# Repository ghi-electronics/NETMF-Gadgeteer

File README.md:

# NETMF-Gadgeteer

This is the repository for our .NET Gadgeteer drivers. While we are keeping it up, it is no longer being actively maintained.

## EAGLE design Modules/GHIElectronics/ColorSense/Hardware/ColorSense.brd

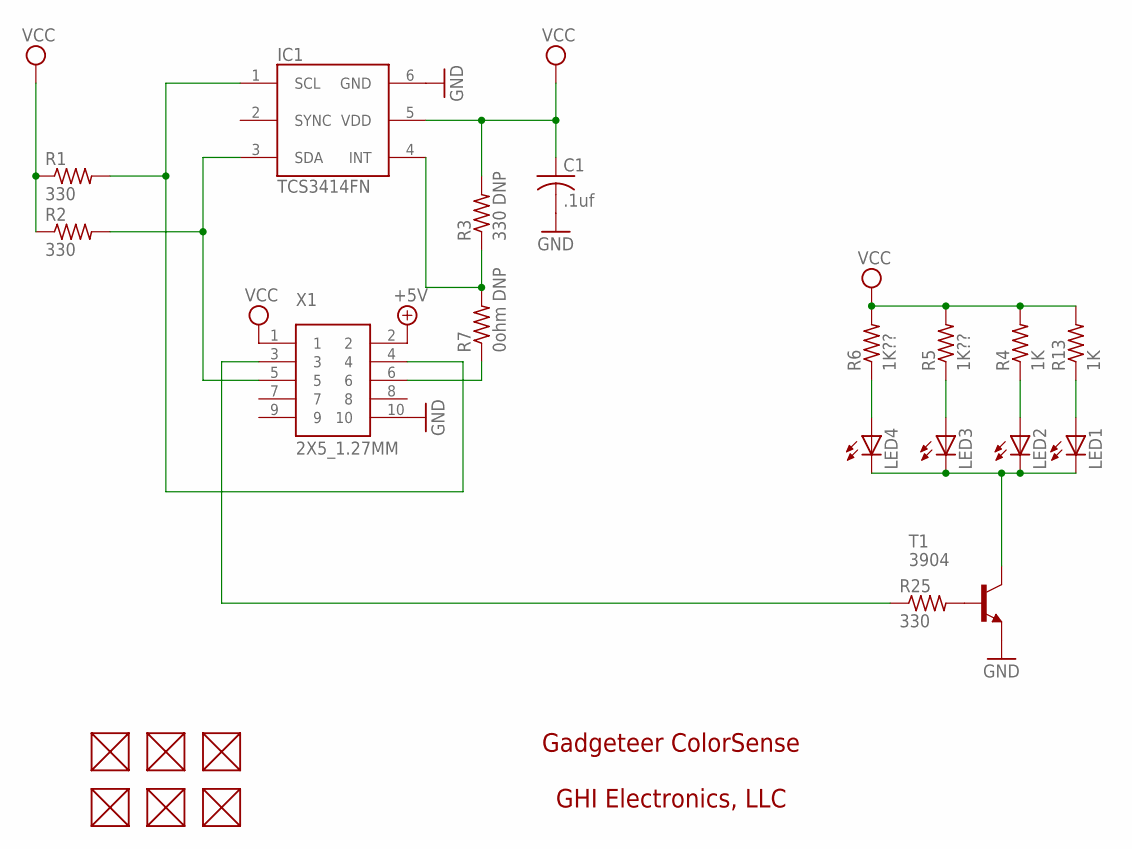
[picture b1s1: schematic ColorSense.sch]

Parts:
C1: .1uf; C0603K
FUD1, FUD2, FUD3, FUD4, FUD5, FUD6: FIDUCIAL; FIDUCIAL_40MIL
IC1: TCS3414FN; DFN-6
LED1, LED2, LED3, LED4: LEDCHIPLED_0805; CHIPLED_0805
R1, R2, R25: 330; R0603
R3: 330 DNP; R0603
R4, R13: 1K; R0603
R5, R6: 1K??; R0603
R7: 0ohm DNP; R0603
T1: 3904; SOT23-BEC
X1: 2X5_1.27MM

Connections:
+5V: X1.2
BACKLIGHT: R25.1, X1.3
GND: C1.2, IC1.6 (GND), T1.E, X1.10
LED-: LED1.C, LED2.C, LED3.C, LED4.C, T1.C
unnamed: IC1.4 (INT), R3.1, R7.2
unnamed: IC1.3 (SDA), R2.2, X1.5
unnamed: IC1.1 (SCL), R1.2, X1.4
unnamed: R7.1, X1.6
unnamed: LED2.A, R4.1
unnamed: LED3.A, R5.1
unnamed: LED4.A, R6.1
unnamed: LED1.A, R13.1
unnamed: R25.2, T1.B
VCC: C1.1, IC1.5 (VDD), R1.1, R2.1, R3.2, R4.2, R5.2, R6.2, R13.2, X1.1

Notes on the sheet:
Gadgeteer ColorSense
GHI Electronics, LLC

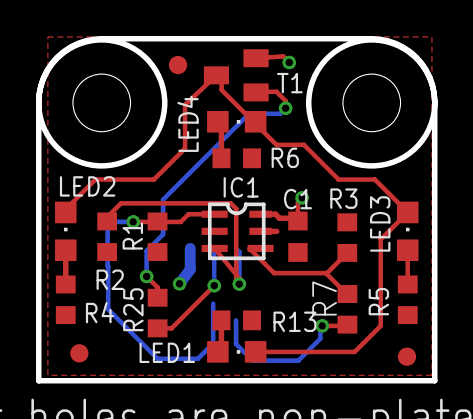
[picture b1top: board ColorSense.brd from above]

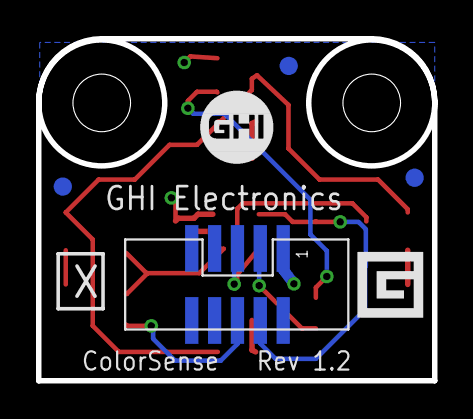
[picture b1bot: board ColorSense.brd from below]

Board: 2 copper layers, 22.0 x 19.0 mm, 23 parts (4 on the bottom side), 13 nets.

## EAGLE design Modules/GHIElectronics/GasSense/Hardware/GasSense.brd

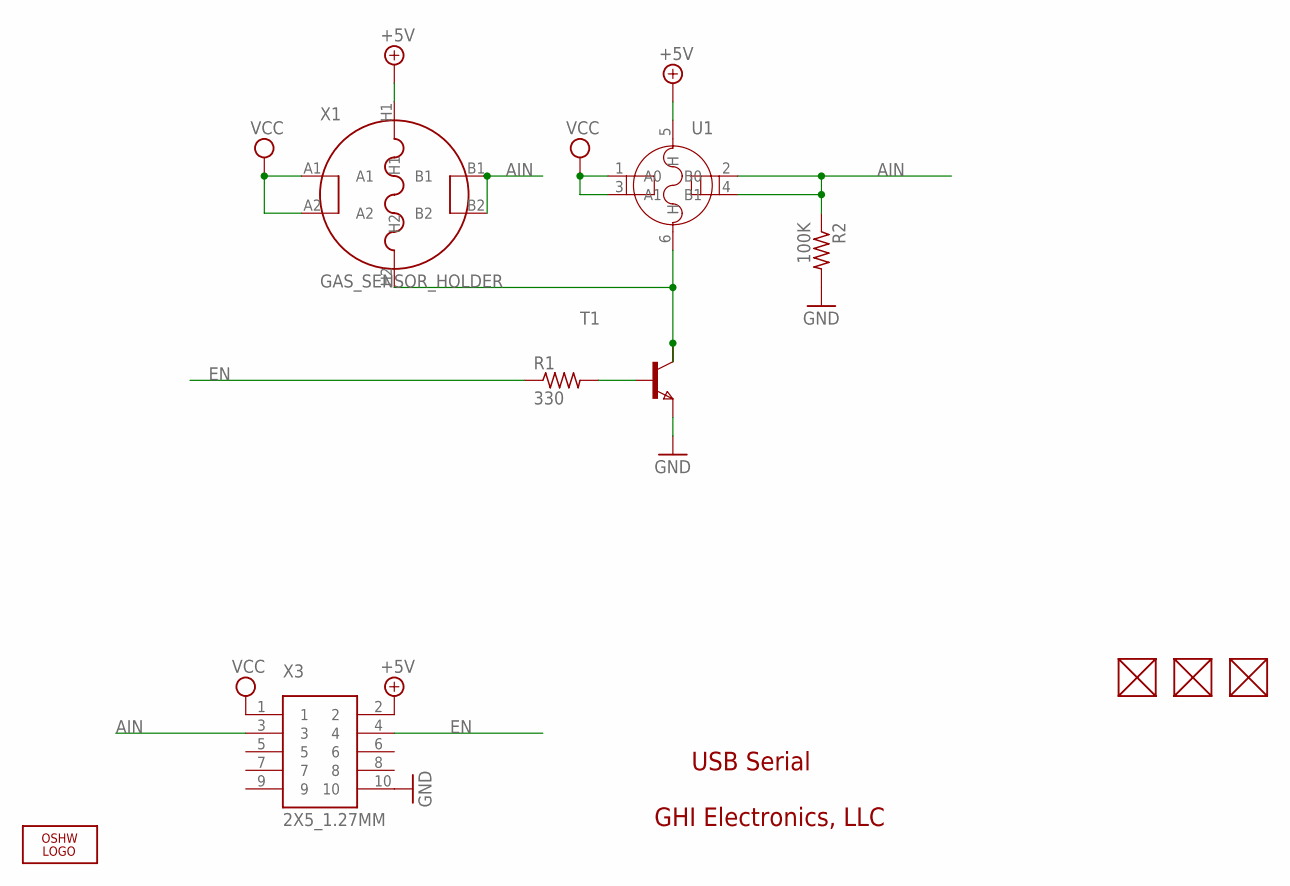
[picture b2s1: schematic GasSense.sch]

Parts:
FUD1, FUD2, FUD3: FIDUCIAL; FIDUCIAL_40MIL
LOGO1: LOGO-OSHW-FILLX0200-NT; OSHW_FILLX200_NOTEXT
R1: 330; R0603
R2: 100K; R0603
T1: NPNSOT223; SOT223
U1: SENSOR-MQ-5; 6P-LEADED-ROUND-D19
X1: GAS_SENSOR_HOLDER
X3: 2X5_1.27MM

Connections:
+5V: U1.5 (H), X1.H1, X3.2
AIN: R2.1, U1.2 (B0), U1.4 (B1), X1.B1, X1.B2, X3.3
EN: R1.1, X3.4
GND: R2.2, T1.3 (E), X3.10
unnamed: R1.2, T1.1 (B)
unnamed: T1.2 (C1), T1.4 (C2), U1.6 (H), X1.H2
VCC: U1.1 (A0), U1.3 (A1), X1.A1, X1.A2, X3.1

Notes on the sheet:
USB Serial
GHI Electronics, LLC

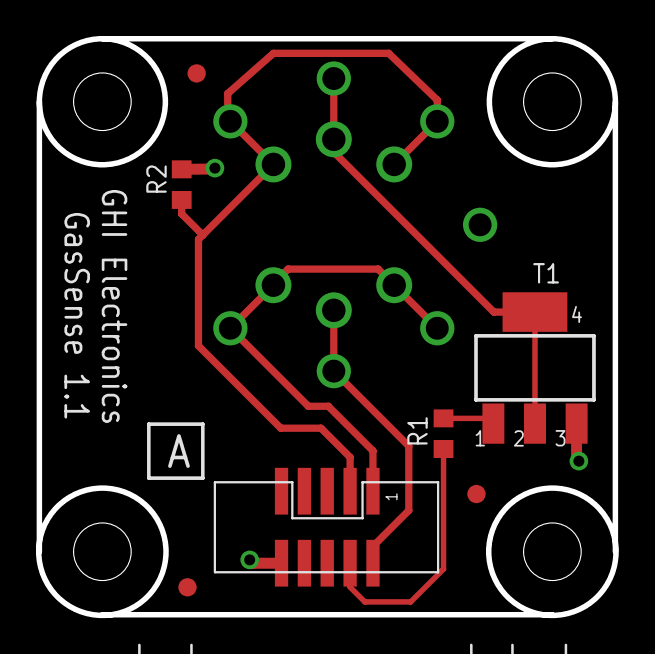
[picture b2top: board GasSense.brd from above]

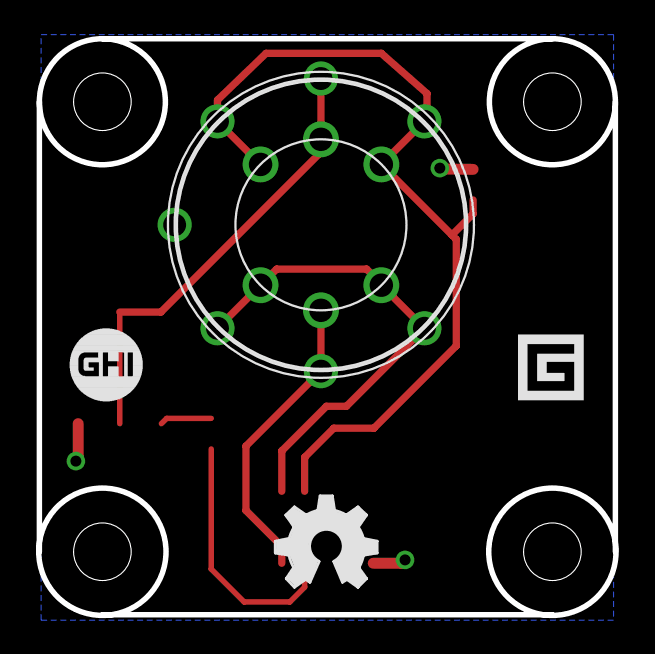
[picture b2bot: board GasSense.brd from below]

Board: 2 copper layers, 32.1 x 32.0 mm, 10 parts (3 on the bottom side), 7 nets.

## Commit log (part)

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2013-07-11 NET-24 #resolve Added ReflectorR3 tester and driver.
2013-07-11 Renamed the TouchC8 buttons.
2013-07-11 NET-27 #resolve Added RS485 tester and driver.
2013-07-15 Removed flow control from the port initialization in RS485.
2013-07-15 NET-23 #comment Started progress on the DAQ driver, still no response from the device.
2013-07-15 Fixed TouchC8 and TouchL12 power ratings.
2013-07-19 Updated RS485 driver.
2013-07-19 Re-added GetJoystickPosition() but marked it as obsolete.
2013-07-22 Updated some project files.
2013-07-22 #NET-51 Added some module images.
2013-07-22 Fixed an issue with WiFi_RN171/GadgeteerHardware.xml where it incorrectly only accepted a K type socket.
2013-07-25 Polished HubAP5 a bit.
2013-07-26 Fixed error messages for AnalogOutput.
2013-07-26 NET-46 #resolve Updated the SDK to Gadgeteer core version 800.
2013-07-31 Fixed a casting issue.
2013-08-07 Fixed the Tunes playback thread.
2013-08-14 Fixed a few socket type bugs in CerbuinoNet and Spider II.
2013-08-15 Updated DisplayN18 solution.
2013-08-15 Fixed TouchL12 guids.
2013-08-15 Fixed Spider II directory structure.
2013-08-15 Added FEZtive to the SDK.
2013-08-15 Fixed FEZtive_42.cs SetAll(Color[]) function
2013-08-19 Updated files for next beta attempt.
2013-08-23 Various bug fixes and tweaks for the SDK.
2013-08-27 Updated Spider II pins and image and updated HubAP5 so that glitchFilter = on no longer throws an exception.
2013-09-04 Increased the CP7 pixel clock divider to 5 from 3 as it was giving trouble with the G120.
2013-09-04 Fixed a bug with socket numbers and premium libraries for the Raptor.
2013-09-11 NET-102 #resolve Worked around the Gadgeteer SPI bug in the music module.
2013-09-11 NET-90 #resolve Added channel band and spacing control.
2013-09-18 NET-38 Added ButtonS7 image, added EnsureTypeIsSupported, and fix socket position.
2013-09-18 Fixed SpiderII AOut precision.
2013-09-20 Removed the ReadMe files.
2013-09-25 NET-23 Added DAQ8B module. Still needs image.
2013-10-01 MET-120 #resolve Fixed the DAQ channels.
2013-10-03 Fixed Cobra II and RN171 shared pins.
2013-10-11 Fixed Display N7 corruption on G120.
2013-10-23 Updated release notes and remopved pull down resistors from the DistanceUS3.
2013-11-18 Fixed Raptor bitmap callback.
2013-12-09 NET-40 #resolve Added a controllable frequency and improved the non-blocking function for the MotorController.
2013-12-11 Removed the pull down resistors from ButtonS7 and improved HubAP5 a bit.
2014-01-03 Fixed a null reference exception in Tunes.Stop
2014-01-07 Removed an un-needed pin reservation.
2014-01-16 NET-127 Added 4.3 projects for each module and mainboard. Still need to be updated to the Gadgeteer 4.3 API.
2014-01-17 Updated drivers to the 4.3 Gadgeteer API.
2014-01-20 NET-127 Updated the copyright year and assembly versioning.
2014-01-20 NET-127 Updated the MSI and MSM files.
2014-01-20 NET-127 Updated GadgeteerHardware.
2014-01-21 NET-127 Updated some installer projects.
2014-01-28 Updated release notes.
2014-01-30 Added SPlus assembly info.
2014-02-06 Fixed some bugs in RN171
2014-02-13 Updated some mainboard Gadgeteer hardware files.
2014-02-13 Updated GHI libraries to use underscores.
2014-02-18 Removed unneeded icons.
2014-02-19 Updated some Gadgeteer hardware files for 4.2.
2014-02-19 Moved the ELM and WiFly shared code into each NETMF version project because they are dependent on Gadgeteer.
2014-02-19 Added some old modules back.
2014-02-19 Lowercased instance name of modules.
2014-02-19 Added some missing things to the msm files.
2014-02-20 Updated some references.
2014-02-20 Few tweaks to GadgeteerHardwares.
2014-02-27 Updated some project references.
2014-02-28 Updated assembly references to use the new assemblies with periods.
2014-02-28 Corrected some assembly names.
2014-03-13 Removed Ref.s to TinyCLR
2014-03-26 Removed some discontinued modules.
2014-03-26 Removed LEDMatrix.
2014-03-26 NET-184 #resolve Fixed DaisyLink sockets in GadgeteerHardware.xml
2014-03-27 Updated the modules to use the new libraries.
2014-04-08 Updated mainboards to use the module shared files when possible and updated to the latest GHI libraries.
2014-04-14 Improved the Hydra, Raptor, Spider, and Spider II mainboards.
2014-04-15 Improved the Cobra and Cerberus mainboards.
2014-04-15 Improved the networking modules.
2014-04-15 Improved the displays.
2014-04-15 Improved the LED modules.
2014-04-15 Improved the relays.
2014-04-15 Improved USBHost.
2014-04-16 Improved the camera.
2014-04-16 Improved the flash module.
2014-04-17 Improved the RS485 and RS232.
2014-04-17 Improved the USBClient DP and SP.
2014-04-17 Improved some more modules.
2014-04-18 Improved PulseInOut and RadioFM1.
2014-04-18 Improved VideoOut and OBDII.
2014-04-18 Removed EVE800.
2014-04-18 Added the NullModem driver.
2014-04-18 Added an indirected socket to the extender.
2014-04-21 Improved the music module.
2014-04-21 Improved the GPS and Gyro.
2014-04-21 Updated the hardware versions in the Stepper and WiFi.
2014-04-22 Improved WiFiRN171 some.
2014-04-23 Finished improving the WiFi RN171.
2014-04-23 Fixed some event bugs in the CP7.
2014-04-28 A few bug fixes.
2014-04-29 Fixed some project references and updated versions.
2014-05-01 Fixed socket order in the G400HDR.
2014-05-13 Fixed a few driver bugs.
2014-05-13 Removes the font and resource files from the testers.
2014-05-28 Added the RelayX1 tester.
2014-05-28 Re-added the relay tester.
2014-05-28 Updated the mainboard testers.
2014-05-28 Added startup info to all of the module testers.
2014-05-28 updated some testers.
2014-05-30 Changed the font used in testers.
2014-06-02 Added ButtonS7 tester.
2014-06-11 Added Cerberus 4.3 mainboards.
2014-06-12 Fixed some tunes bugs and added a tester for it.
2014-06-17 Moved a lot of drivers to a legacy SDK.
2014-06-17 Moved Cobra II to legacy.
2014-06-17 Refactored some Seeed modules.
2014-06-18 Added more legacy modules to the Gadgeteer Legacy SDK.
2014-06-18 Fixed some paths in the legacy drivers.
2014-06-18 * Improve SerCam driver
2014-06-19 Improved SerCam Driver
2014-06-19 Tweaked SerCam exception.
2014-06-19 Added some testers.
2014-06-20 Fixed Cobra II Eco and added some testers.
2014-06-24 Added LightSense tester.
2014-06-25 Fixed setting the display orientation.
2014-06-25 Updated testers to 4.3.2.0 and added USBHost tester.
2014-07-07 Added the Button tester.
2014-07-16 Few bug fixes.
2014-07-17 Tweaked the AccelG248 and added a tester for it.
2014-07-17 Tweaked a tester.
2014-07-18 Improved the RFID reader.
2014-07-22 Updated to latest drivers and removed TempHumidity.
2014-07-22 Added TempHumidity to the legacy SDK.
2014-07-24 Defaulted to 9800 baud for serial and changed TempHumidSI70 to XY socket.
2014-07-24 Added SDCard features to Cobra II.
2014-07-24 Mounting and unmounting SD cards return bools.
2014-07-24 Improved storage device handling in the mainboards.
2014-07-24 Start the USB controller by default.
2014-07-25 Improved the USBHost and SDCard modules.
2014-07-25 Cleaned up SDCard support for the Cerbuinos and CobraII.
2014-07-25 Added USBHost to the Cerbuinos and Cobra II.
2014-07-29 Fixed SD card detection pin, updated some legacy mainboards, updated versions.
2014-07-30 Removed the mass storage mount functions from the boards with USB since its redundant and changed the SDCard detect on the Cobra to be an input port since its pin doesn't support interrupts.
2014-07-31 Added HubAP5 tester and updated DisplayTE35 tester.
2014-07-31 Updated some instruction text.
2014-08-01 Removed XBeeLib.
2014-08-07 Updated TempHumidSI70 tester.
2014-08-07 Updated TempHumidSI70 image.
2014-08-14 Fixed a bug in camera streaming.
2014-08-19 Fixed a socket bug.
2014-08-20 Added pin definitions for the header rows of the Cerbuinos.
2014-08-20 No longer open the network interface in the module constructor. Gives the user a chance to set the mac address.
2014-08-21 Properly set the control pin in Cerberus native spi display handler.
2014-08-21 Added a missing pin to a tester.
2014-08-21 Changed the legacy folders to discontinued and removed the legacy mainboards.
2014-08-28 Added the Hydra tester.
2014-09-03 Added USBHost to the Cerb Family boards and updated the versions.
2014-09-11 Fixed the extender socket and removed the text from the FEZ Spider image.
2014-09-16 Added a WiFiRS21 tester.
2014-09-18 Added USBSerialSP tester.
2014-10-01 Reduced a lot of the module and mainboard image sizes.
2014-10-13 Fixed a version number.
2014-10-13 Added a delay to SD card mounting.
2014-10-15 Cleaned up the cellular radio driver some.
2014-10-21 Fixed a reference version.
2014-10-22 Updated version.
2014-10-23 Fixed Extender analog in and out.
2014-11-20 Switched to context 1 in cellular radio.
2014-11-21 Fixed the COM port on socket 1 of the Cerbuino Net.
2014-11-21 Reworked response parsing on the cellular radio module.
2014-11-25 Added the discontinued modules to the main SDK but marked them as obsolete.
2014-11-25 Marked the Cobra IIs obsolete.
2014-11-25 Added 4.3 to some obsolete drivers.
2014-11-25 Cleaned up a few modules.
2014-11-26 Fixed two music module bugs.
2014-12-02 Fixed 4.3 cerb family analog output.
2014-12-03 Fixed some CurrentACS issues.
2014-12-04 Fixed a typo in CurrentACS.
2014-12-09 Changed the duty cycle after the tunes is done playing to stop a low hum from being improperly played.
2014-12-17 Improved SMS handling in the cellular radio.
2015-01-05 Fixed infinite playing and a variable name in Tunes.
2015-01-06 Fixed some reference versions.
2015-01-09 Fixed HD44780 image orientation.
2015-01-12 Fixed help urls.
2015-01-13 Fixed EBlockExpansion hardware definition file.
2015-02-04 Fixed the USB Client EDP hardware file.
2015-02-24 Fixed handling of counts around 0 in the RotaryEncoder.
2015-03-09 Allowed use of all clock sources in the Hub AP5 for better PWM generation.
2015-03-17 Removed a version attribute.
2015-03-18 Added a solution file.
2015-03-30 Formatted the 4.3 drivers.
2015-03-31 Fixed the rest tone in Tunes.
2015-04-03 Fixed Display T35 display name.
2015-04-08 Fixed Hydra supported socket types.
2015-04-09 Added an overload to allow customizing PPP initialization.
2015-04-09 Added SendATCommand with expected response.
2015-04-09 Fixed the power up state check.
2015-04-09 Fixed CellularRadio power consumption.
2015-04-10 Removed SpecialPurposePin.
2015-04-10 Commit for SDK release 2015.1.4.0
2015-04-14 Fixed unnumbered pins on mainboards and usb modules.
2015-04-23 Commit for SDK release 2015.1.5.0
2015-04-28 Commit for SDK release 2015.1.6.0
2015-05-18 Fixed Cobra II Eco socket placement.
2015-06-03 Commit for SDK release 2015.1.8.0
2015-06-18 Added FEZReaper.
2015-06-19 Added FEZ Spider II.
2015-06-19 Updated socket placement.
2015-06-26 Fixed an assembly reference.
2015-06-26 Commit for SDK release 2015.1.9.0
2015-07-06 Added FEZMedusaII.
2015-07-10 Fixed Spider II SPI socket pins.
2015-07-14 Fixed a few bugs in Tunes.
2015-07-22 Fixed a pin on the Reaper.
2015-07-22 Updated FEZ Reaper image.
2015-07-27 Removed a few unneeded things from MedusaII.
2015-07-27 Updated Medusa II image.
2015-07-27 Removed Medusa II from the build.
2015-09-10 Fixed Spider II mainboard analog input precision.
2015-11-16 Removed G400 SPI1 GPIO pins.
2015-11-16 Fixed G120 SPI2 GPIO definition.
2015-11-16 Updated G400 boards to use the new G400 pin definitions.
2015-12-02 Updated mainboards to the latest display changes and swapped 90 and 270 rotation on the N18.
2015-12-04 Improved cellular radio power on detection, CREG and CGREG response parsing, and phone number + prefixing.
2015-12-21 Fixed result scaling in AccelG248 and preallocated the read buffers.
2015-12-24 Commit for SDK release 2016.1.0.0
2016-01-04 Fixed CellularRadio socket position.
2016-03-22 Marked some modules as obsolete that were missed.
2016-03-23 Fixed the initial PWM settings on the HubAP5.
2016-03-24 Fixed TouchC8 WheelPositionChanged event raising.
